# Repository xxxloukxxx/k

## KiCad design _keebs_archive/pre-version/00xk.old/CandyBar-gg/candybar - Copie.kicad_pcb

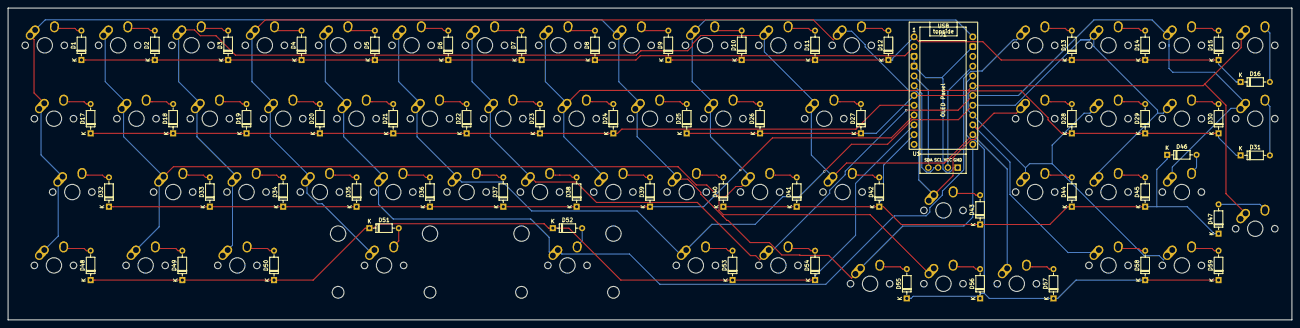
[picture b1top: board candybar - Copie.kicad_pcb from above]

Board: 2 copper layers, 333.4 x 81.0 mm, 120 parts (0 on the bottom side), 79 nets.

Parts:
D1, D2, D3, D4, D5, D6, D7, D8, D9, D10, D11, D12, D13, D14, D15, D16, D17, D18, D19, D20, D21, D22, D23, D24, D25, D26, D27, D28, D29, D30, D31, D32, D33, D34, D35, D36, D37, D38, D39, D40, D41, D42, D43, D44, D45, D46, D47, D48, D49, D50, D51, D52, D53, D54, D55, D56, D57, D58, D59: 1N4148; D_DO-35_SOD27_P7.62mm_Horizontal
J1: Conn_01x04_Socket; SSD1306-0.91-OLED-4pin-128x32
MX1, MX2, MX3, MX4, MX5, MX6, MX7, MX8, MX9, MX10, MX11, MX12, MX13, MX14, MX15, MX16, MX18, MX19, MX20, MX21, MX22, MX23, MX24, MX25, MX26, MX28, MX29, MX30, MX31, MX33, MX34, MX35, MX36, MX37, MX38, MX39, MX40, MX41, MX43, MX44, MX45, MX46, MX47, MX55, MX56, MX57, MX58, MX59: MX; MX-Alps-Hybrid-1U
MX17, MX42, MX48, MX49, MX50, MX53, MX54: MX; MX-Alps-Hybrid-1.25U
MX27, MX32: MX; MX-Alps-Hybrid-1.75U
MX51: MX; MX-Alps-Hybrid-2.75U-ReversedStabilizers
MX52: MX; MX-Alps-Hybrid-2.25U-ReversedStabilizers
U1: ProMicro; ProMicro_USBup

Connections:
COL1: MX1.1 (COL), MX9.1 (COL), MX17.1 (COL), MX25.1 (COL), MX32.1 (COL), MX40.1 (COL), MX48.1 (COL), MX55.1 (COL), U1.24 (B6)
COL2: MX2.1 (COL), MX10.1 (COL), MX18.1 (COL), MX26.1 (COL), MX33.1 (COL), MX41.1 (COL), MX49.1 (COL), MX56.1 (COL), U1.13 (B0)
COL3: MX3.1 (COL), MX11.1 (COL), MX19.1 (COL), MX27.1 (COL), MX34.1 (COL), MX42.1 (COL), MX50.1 (COL), MX57.1 (COL), U1.23 (B2)
COL4: MX4.1 (COL), MX12.1 (COL), MX20.1 (COL), MX28.1 (COL), MX35.1 (COL), MX43.1 (COL), MX51.1 (COL), MX58.1 (COL), U1.22 (B3)
COL5: MX5.1 (COL), MX13.1 (COL), MX21.1 (COL), MX29.1 (COL), MX36.1 (COL), MX44.1 (COL), MX52.1 (COL), MX59.1 (COL), U1.21 (B1)
COL6: MX6.1 (COL), MX14.1 (COL), MX22.1 (COL), MX30.1 (COL), MX37.1 (COL), MX45.1 (COL), MX53.1 (COL), U1.20 (F7)
COL7: MX7.1 (COL), MX15.1 (COL), MX23.1 (COL), MX31.1 (COL), MX38.1 (COL), MX46.1 (COL), MX54.1 (COL), U1.19 (F6)
COL8: MX8.1 (COL), MX16.1 (COL), MX24.1 (COL), MX39.1 (COL), MX47.1 (COL), U1.18 (F5)
GND: J1.1, U1.3 (GND), U1.4 (GND), U1.14 (GND)
unnamed: D1.2 (A), MX1.2 (ROW)
unnamed: D2.2 (A), MX2.2 (ROW)
unnamed: D3.2 (A), MX3.2 (ROW)
unnamed: D4.2 (A), MX4.2 (ROW)
unnamed: D5.2 (A), MX5.2 (ROW)
unnamed: D6.2 (A), MX6.2 (ROW)
unnamed: D7.2 (A), MX7.2 (ROW)
unnamed: D8.2 (A), MX8.2 (ROW)
unnamed: D9.2 (A), MX9.2 (ROW)
unnamed: D10.2 (A), MX10.2 (ROW)
unnamed: D11.2 (A), MX11.2 (ROW)
unnamed: D12.2 (A), MX12.2 (ROW)
unnamed: D13.2 (A), MX13.2 (ROW)
unnamed: D14.2 (A), MX14.2 (ROW)
unnamed: D15.2 (A), MX15.2 (ROW)
unnamed: D16.2 (A), MX16.2 (ROW)
unnamed: D17.2 (A), MX17.2 (ROW)
unnamed: D18.2 (A), MX18.2 (ROW)
unnamed: D19.2 (A), MX19.2 (ROW)
unnamed: D20.2 (A), MX20.2 (ROW)
unnamed: D21.2 (A), MX21.2 (ROW)
unnamed: D22.2 (A), MX22.2 (ROW)
unnamed: D23.2 (A), MX23.2 (ROW)
unnamed: D24.2 (A), MX24.2 (ROW)
unnamed: D25.2 (A), MX25.2 (ROW)
unnamed: D26.2 (A), MX26.2 (ROW)
unnamed: D27.2 (A), MX27.2 (ROW)
unnamed: D28.2 (A), MX28.2 (ROW)
unnamed: D29.2 (A), MX29.2 (ROW)
unnamed: D30.2 (A), MX30.2 (ROW)
unnamed: D31.2 (A), MX31.2 (ROW)
unnamed: D32.2 (A), MX32.2 (ROW)
unnamed: D33.2 (A), MX33.2 (ROW)
unnamed: D34.2 (A), MX34.2 (ROW)
unnamed: D35.2 (A), MX35.2 (ROW)
unnamed: D36.2 (A), MX36.2 (ROW)
unnamed: D37.2 (A), MX37.2 (ROW)
unnamed: D38.2 (A), MX38.2 (ROW)
unnamed: D39.2 (A), MX39.2 (ROW)
unnamed: D40.2 (A), MX40.2 (ROW)
unnamed: D41.2 (A), MX41.2 (ROW)
unnamed: D42.2 (A), MX42.2 (ROW)
unnamed: D43.2 (A), MX43.2 (ROW)
unnamed: D44.2 (A), MX44.2 (ROW)
unnamed: D45.2 (A), MX45.2 (ROW)
unnamed: D46.2 (A), MX46.2 (ROW)
unnamed: D47.2 (A), MX47.2 (ROW)
unnamed: D48.2 (A), MX48.2 (ROW)
unnamed: D49.2 (A), MX49.2 (ROW)
unnamed: D50.2 (A), MX50.2 (ROW)
unnamed: D51.2 (A), MX51.2 (ROW)
unnamed: D52.2 (A), MX52.2 (ROW)
unnamed: D53.2 (A), MX53.2 (ROW)
unnamed: D54.2 (A), MX54.2 (ROW)
unnamed: D55.2 (A), MX55.2 (ROW)
unnamed: D56.2 (A), MX56.2 (ROW)
unnamed: D57.2 (A), MX57.2 (ROW)
unnamed: D58.2 (A), MX58.2 (ROW)
unnamed: D59.2 (A), MX59.2 (ROW)
ROW1: D1.1 (K), D2.1 (K), D3.1 (K), D4.1 (K), D5.1 (K), D6.1 (K), D7.1 (K), D8.1 (K), U1.2 (D2-RX)
ROW2: D9.1 (K), D10.1 (K), D11.1 (K), D12.1 (K), D13.1 (K), D14.1 (K), D15.1 (K), D16.1 (K), U1.1 (D3-TX)
ROW3: D17.1 (K), D18.1 (K), D19.1 (K), D20.1 (K), D21.1 (K), D22.1 (K), D23.1 (K), D24.1 (K), U1.8 (C6)
ROW4: D25.1 (K), D26.1 (K), D27.1 (K), D28.1 (K), D29.1 (K), D30.1 (K), D31.1 (K), U1.7 (D4)
ROW5: D32.1 (K), D33.1 (K), D34.1 (K), D35.1 (K), D36.1 (K), D37.1 (K), D38.1 (K), D39.1 (K), U1.9 (D7)
ROW6: D40.1 (K), D41.1 (K), D42.1 (K), D43.1 (K), D44.1 (K), D45.1 (K), D46.1 (K), D47.1 (K), U1.11 (B4)
ROW7: D48.1 (K), D49.1 (K), D50.1 (K), D51.1 (K), D52.1 (K), D53.1 (K), D54.1 (K), U1.10 (E6)
ROW8: D55.1 (K), D56.1 (K), D57.1 (K), D58.1 (K), D59.1 (K), U1.17 (F4)
SCL: J1.3, U1.6 (D0)
SDA: J1.4, U1.5 (D1)
VCC: J1.2, U1.16 (VCC)

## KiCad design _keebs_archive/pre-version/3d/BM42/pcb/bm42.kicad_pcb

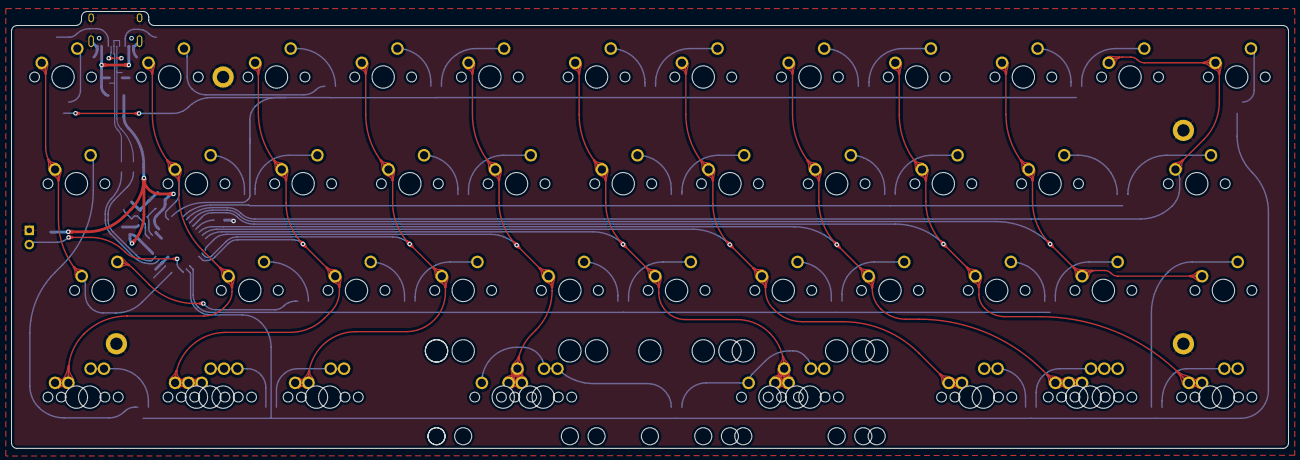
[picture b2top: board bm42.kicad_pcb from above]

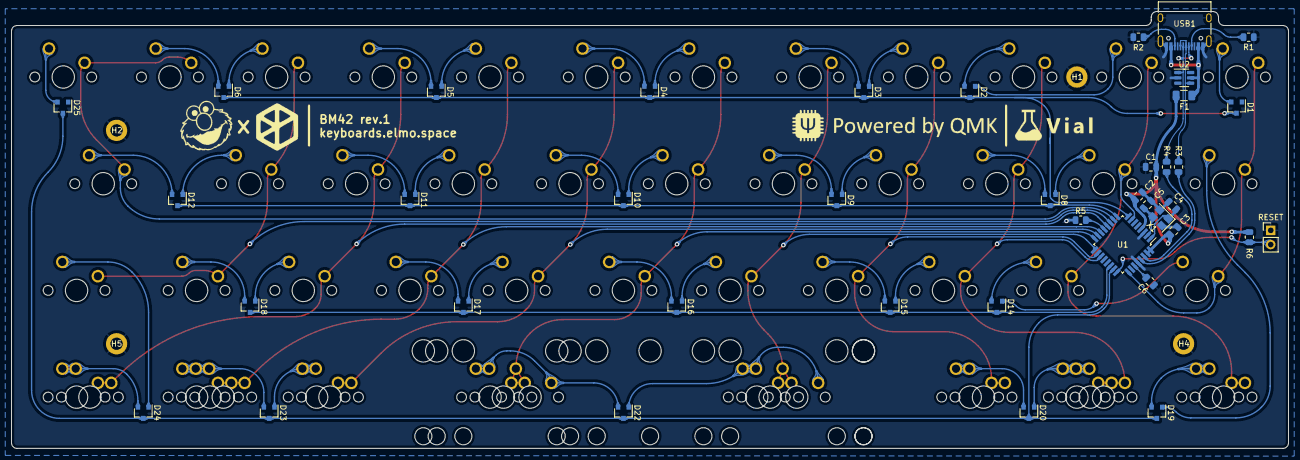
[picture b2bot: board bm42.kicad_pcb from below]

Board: 2 copper layers, 228.0 x 78.0 mm, 98 parts (44 on the bottom side), 71 nets.

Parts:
C1: 10uF; C_0805_2012Metric
C2, C3: 0.1uF; C_0805_2012Metric
C4, C5: 22pF; C_0805_2012Metric
C6: 1uF; C_0805_2012Metric
D1, D2, D3, D4, D5, D6, D8, D9, D10, D11, D12, D14, D15, D16, D17, D18, D19, D20, D22, D23, D24, D25: D_Small; D_SOT-23_ANK_norm
F1: Polyfuse_Small; Fuse_1206_3216Metric
H1, H2, H4, H5: MountingHole_Pad; MountingHole_2.2mm_M2_DIN965_Pad
MX1, MX2, MX3, MX4, MX5, MX6, MX7, MX8, MX9, MX10, MX11, MX13, MX14, MX15, MX16, MX17, MX18, MX19, MX20, MX21, MX24, MX25, MX26, MX27, MX28, MX29, MX30, MX31, MX32, MX35, MX41, MX43, MX50, MX51, MX52, MX54: MX-NoLED; MXOnly-1U-NoLED
MX12, MX33, MX34, MX36, MX40, MX42, MX49, MX53: MX-NoLED; MXOnly-1.25U-NoLED
MX22, MX23: MX-NoLED; MXOnly-1.75U-NoLED
MX37: MX-NoLED; MXOnly-3U-ReversedStabilizers-NoLED
MX39: MX-NoLED; MXOnly-2U-ReversedStabilizers-NoLED
MX44, MX47: MX-NoLED; MXOnly-2.75U-ReversedStabilizers-NoLED
MX45, MX46: MX-NoLED; MXOnly-2.25U-ReversedStabilizers-NoLED
MX48, MX55: MX-NoLED; MXOnly-1.5U-NoLED
R1, R2: 5.1k; R_0805_2012Metric
R3, R4: 22; R_0805_2012Metric
R5, R6: 10k; R_0805_2012Metric
RESET: RESET; PinHeader_1x02_P2.54mm_Vertical
U1: ATmega32U2-A; TQFP-32_7x7mm_P0.8mm
U2: SRV05-4; SOT-23-6
USB1: USB_C_Receptacle_USB2.0; USB_C_Receptacle_HRO_TYPE-C-31-M-12
X1: Crystal_GND24_Small; Crystal_SMD_3225-4Pin_3.2x2.5mm

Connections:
+5V: C1.1, C2.1, C3.1, F1.1, R6.2, U1.4 (VCC), U1.31 (UVCC), U1.32 (AVCC)
D+: R3.1, U2.4 (IO3), USB1.A6 (D+), USB1.B6 (D+)
D-: R4.1, U2.1 (IO1), USB1.A7 (D-), USB1.B7 (D-)
GND: C1.2, C2.2, C3.2, C4.2, C5.2, C6.2, H1.1, H2.1, H4.1, H5.1, R1.1, R2.1, R5.1, RESET.1, U1.3 (GND), U1.28 (UGND), U2.2 (VN), USB1.A1 (GND), USB1.A12 (GND), USB1.B1 (GND), USB1.B12 (GND), USB1.S1 (SHIELD), X1.2, X1.4
unnamed: C4.1, U1.1 (XTAL1), X1.1
unnamed: C5.1, U1.2 (PC0/XTAL2), X1.3
unnamed: C6.1, U1.27 (UCAP)
unnamed: D1.3 (A2), MX1.2 (ROW)
unnamed: D2.2 (A1), MX2.2 (ROW)
unnamed: D2.3 (A2), MX3.2 (ROW)
unnamed: D3.2 (A1), MX4.2 (ROW)
unnamed: D3.3 (A2), MX5.2 (ROW)
unnamed: D4.2 (A1), MX6.2 (ROW)
unnamed: D4.3 (A2), MX7.2 (ROW)
unnamed: D5.2 (A1), MX8.2 (ROW)
unnamed: D5.3 (A2), MX9.2 (ROW)
unnamed: D6.2 (A1), MX10.2 (ROW)
unnamed: D6.3 (A2), MX11.2 (ROW)
unnamed: D8.2 (A1), MX13.2 (ROW)
unnamed: D8.3 (A2), MX14.2 (ROW)
unnamed: D9.2 (A1), MX15.2 (ROW)
unnamed: D9.3 (A2), MX16.2 (ROW)
unnamed: D10.2 (A1), MX17.2 (ROW)
unnamed: D10.3 (A2), MX18.2 (ROW)
unnamed: D11.2 (A1), MX19.2 (ROW)
unnamed: D11.3 (A2), MX20.2 (ROW)
unnamed: D12.2 (A1), MX21.2 (ROW)
unnamed: D12.3 (A2), MX22.2 (ROW)
unnamed: D14.2 (A1), MX23.2 (ROW)
unnamed: D14.3 (A2), MX24.2 (ROW)
unnamed: D15.2 (A1), MX25.2 (ROW)
unnamed: D15.3 (A2), MX26.2 (ROW)
unnamed: D16.2 (A1), MX27.2 (ROW)
unnamed: D16.3 (A2), MX28.2 (ROW)
unnamed: D17.2 (A1), MX29.2 (ROW)
unnamed: D17.3 (A2), MX30.2 (ROW)
unnamed: D18.2 (A1), MX31.2 (ROW)
unnamed: D18.3 (A2), MX32.2 (ROW)
unnamed: D19.2 (A1), MX12.2 (ROW)
unnamed: D19.3 (A2), MX34.2 (ROW), MX48.2 (ROW)
unnamed: D20.2 (A1), MX35.2 (ROW), MX49.2 (ROW), MX50.2 (ROW)
unnamed: D20.3 (A2), MX36.2 (ROW), MX51.2 (ROW)
unnamed: D23.2 (A1), MX40.2 (ROW), MX52.2 (ROW)
unnamed: D23.3 (A2), MX41.2 (ROW), MX53.2 (ROW), MX54.2 (ROW)
unnamed: D24.2 (A1), MX33.2 (ROW)
unnamed: D24.3 (A2), MX42.2 (ROW), MX55.2 (ROW)
unnamed: D25.3 (A2), MX43.2 (ROW)
unnamed: R1.2, USB1.A5 (CC1)
unnamed: R2.2, USB1.B5 (CC2)
unnamed: R3.2, U1.29 (D+)
unnamed: R4.2, U1.30 (D-)
unnamed: R5.2, U1.13 (~HWB/PD7)
unnamed: R6.1, RESET.2, U1.24 (PC1/~RESET)
VCC: F1.2, U2.5 (VP), USB1.A4 (VBUS), USB1.A9 (VBUS), USB1.B4 (VBUS), USB1.B9 (VBUS)
col0: MX1.1 (COL), MX12.1 (COL), MX23.1 (COL), U1.25 (PC5)
col1: MX2.1 (COL), MX13.1 (COL), MX24.1 (COL), MX34.1 (COL), MX48.1 (COL), U1.7 (PD1)
col2: MX3.1 (COL), MX14.1 (COL), MX25.1 (COL), MX35.1 (COL), MX49.1 (COL), MX50.1 (COL), U1.19 (PB5)
col3: MX4.1 (COL), MX15.1 (COL), MX26.1 (COL), MX36.1 (COL), MX51.1 (COL), U1.18 (PB4)
col4: MX5.1 (COL), MX16.1 (COL), MX27.1 (COL), MX37.1 (COL), MX44.1 (COL), MX46.2 (ROW), U1.17 (PB3)
col5: MX6.1 (COL), MX17.1 (COL), MX28.1 (COL), MX39.1 (COL), MX45.1 (COL), MX47.2 (ROW), U1.16 (PB2)
col6: MX7.1 (COL), MX18.1 (COL), MX29.1 (COL), MX40.1 (COL), MX52.1 (COL), U1.15 (PB1)
col7: MX8.1 (COL), MX19.1 (COL), MX30.1 (COL), MX41.1 (COL), MX53.1 (COL), MX54.1 (COL), U1.14 (PB0)
col8: MX9.1 (COL), MX20.1 (COL), MX31.1 (COL), MX42.1 (COL), MX55.1 (COL), U1.12 (PD6)
col9: MX10.1 (COL), MX21.1 (COL), MX32.1 (COL), MX33.1 (COL), U1.11 (PD5)
col10: MX11.1 (COL), MX22.1 (COL), MX43.1 (COL), U1.10 (PD4)
row0: D1.1 (K), D2.1 (K), D3.1 (K), D4.1 (K), D5.1 (K), D6.1 (K), U1.8 (PD2)
row1: D8.1 (K), D9.1 (K), D10.1 (K), D11.1 (K), D12.1 (K), U1.9 (PD3)
row2: D14.1 (K), D15.1 (K), D16.1 (K), D17.1 (K), D18.1 (K), U1.22 (PC7)
row3: D19.1 (K), D20.1 (K), D22.1 (K), D23.1 (K), D24.1 (K), D25.1 (K), U1.23 (PC6)
spc1: D22.2 (A1), MX37.2 (ROW), MX44.2 (ROW), MX46.1 (COL)
spc2: D22.3 (A2), MX39.2 (ROW), MX45.2 (ROW), MX47.1 (COL)

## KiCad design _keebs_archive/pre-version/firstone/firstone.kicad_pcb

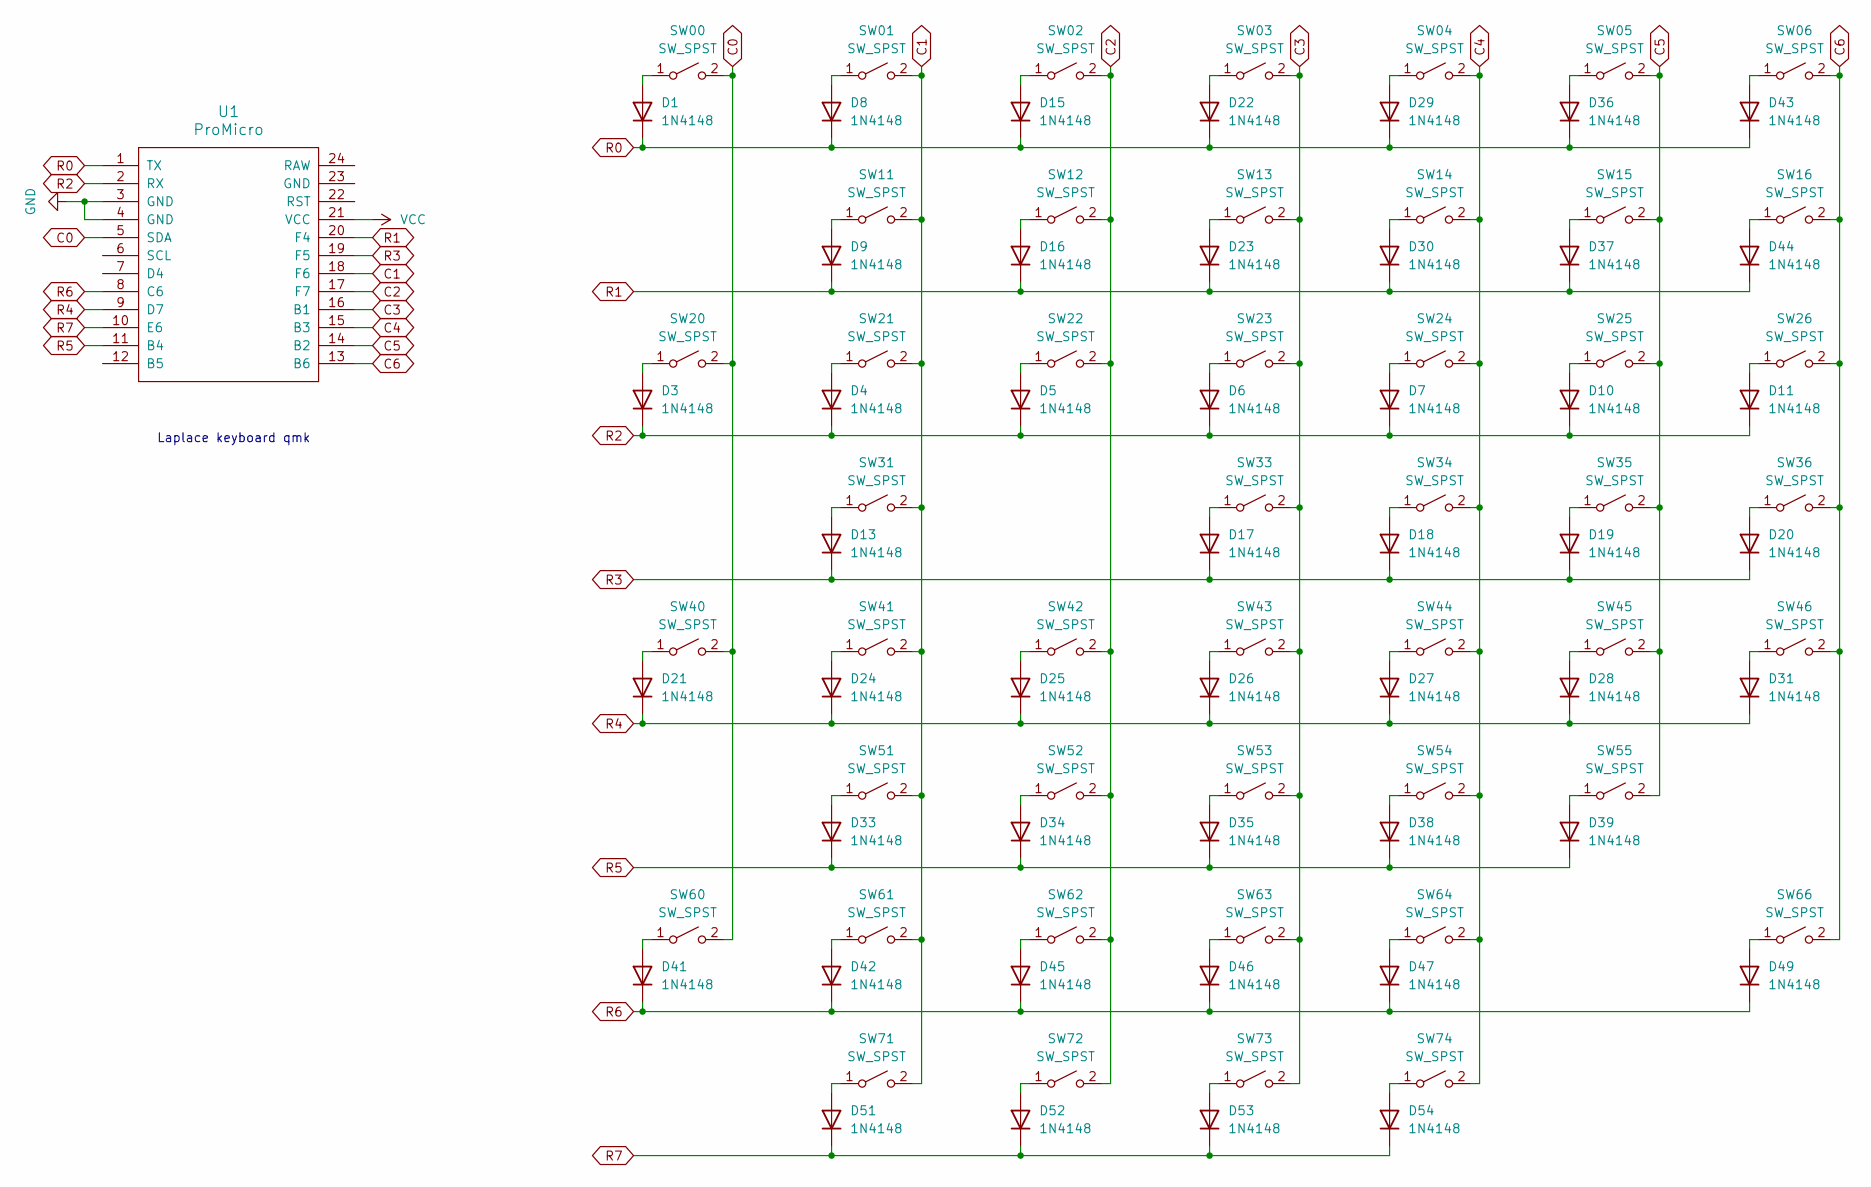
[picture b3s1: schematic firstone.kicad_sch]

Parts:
D1, D3, D4, D5, D6, D7, D8, D9, D10, D11, D13, D15, D16, D17, D18, D19, D20, D21, D22, D23, D24, D25, D26, D27, D28, D29, D30, D31, D33, D34, D35, D36, D37, D38, D39, D41, D42, D43, D44, D45, D46, D47, D49, D51, D52, D53, D54: 1N4148; D_DO-35_SOD27_P7.62mm_Horizontal
SW00, SW01, SW02, SW03, SW04, SW05, SW06, SW11, SW12, SW13, SW14, SW15, SW16, SW20, SW21, SW22, SW23, SW24, SW25, SW26, SW31, SW33, SW34, SW35, SW36, SW40, SW41, SW42, SW43, SW44, SW45, SW46, SW51, SW52, SW53, SW54, SW55, SW60, SW61, SW62, SW63, SW64, SW66, SW71, SW72, SW73, SW74: SW_SPST; SW_Cherry_MX_PCB
U1: ProMicro

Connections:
C0: SW00.2 (B), SW20.2 (B), SW40.2 (B), SW60.2 (B), U1.5 (SDA)
C1: SW01.2 (B), SW11.2 (B), SW21.2 (B), SW31.2 (B), SW41.2 (B), SW51.2 (B), SW61.2 (B), SW71.2 (B), U1.18 (F6)
C2: SW02.2 (B), SW12.2 (B), SW22.2 (B), SW42.2 (B), SW52.2 (B), SW62.2 (B), SW72.2 (B), U1.17 (F7)
C3: SW03.2 (B), SW13.2 (B), SW23.2 (B), SW33.2 (B), SW43.2 (B), SW53.2 (B), SW63.2 (B), SW73.2 (B), U1.16 (B1)
C4: SW04.2 (B), SW14.2 (B), SW24.2 (B), SW34.2 (B), SW44.2 (B), SW54.2 (B), SW64.2 (B), SW74.2 (B), U1.15 (B3)
C5: SW05.2 (B), SW15.2 (B), SW25.2 (B), SW35.2 (B), SW45.2 (B), SW55.2 (B), U1.14 (B2)
C6: SW06.2 (B), SW16.2 (B), SW26.2 (B), SW36.2 (B), SW46.2 (B), SW66.2 (B), U1.13 (B6)
GND: U1.3 (GND), U1.4 (GND)
unnamed: D1.2 (A), SW00.1 (A)
unnamed: D3.2 (A), SW20.1 (A)
unnamed: D4.2 (A), SW21.1 (A)
unnamed: D5.2 (A), SW22.1 (A)
unnamed: D6.2 (A), SW23.1 (A)
unnamed: D7.2 (A), SW24.1 (A)
unnamed: D8.2 (A), SW01.1 (A)
unnamed: D9.2 (A), SW11.1 (A)
unnamed: D10.2 (A), SW25.1 (A)
unnamed: D11.2 (A), SW26.1 (A)
unnamed: D13.2 (A), SW31.1 (A)
unnamed: D15.2 (A), SW02.1 (A)
unnamed: D16.2 (A), SW12.1 (A)
unnamed: D17.2 (A), SW33.1 (A)
unnamed: D18.2 (A), SW34.1 (A)
unnamed: D19.2 (A), SW35.1 (A)
unnamed: D20.2 (A), SW36.1 (A)
unnamed: D21.2 (A), SW40.1 (A)
unnamed: D22.2 (A), SW03.1 (A)
unnamed: D23.2 (A), SW13.1 (A)
unnamed: D24.2 (A), SW41.1 (A)
unnamed: D25.2 (A), SW42.1 (A)
unnamed: D26.2 (A), SW43.1 (A)
unnamed: D27.2 (A), SW44.1 (A)
unnamed: D28.2 (A), SW45.1 (A)
unnamed: D29.2 (A), SW04.1 (A)
unnamed: D30.2 (A), SW14.1 (A)
unnamed: D31.2 (A), SW46.1 (A)
unnamed: D33.2 (A), SW51.1 (A)
unnamed: D34.2 (A), SW52.1 (A)
unnamed: D35.2 (A), SW53.1 (A)
unnamed: D36.2 (A), SW05.1 (A)
unnamed: D37.2 (A), SW15.1 (A)
unnamed: D38.2 (A), SW54.1 (A)
unnamed: D39.2 (A), SW55.1 (A)
unnamed: D41.2 (A), SW60.1 (A)
unnamed: D42.2 (A), SW61.1 (A)
unnamed: D43.2 (A), SW06.1 (A)
unnamed: D44.2 (A), SW16.1 (A)
unnamed: D45.2 (A), SW62.1 (A)
unnamed: D46.2 (A), SW63.1 (A)
unnamed: D47.2 (A), SW64.1 (A)
unnamed: D49.2 (A), SW66.1 (A)
unnamed: D51.2 (A), SW71.1 (A)
unnamed: D52.2 (A), SW72.1 (A)
unnamed: D53.2 (A), SW73.1 (A)
unnamed: D54.2 (A), SW74.1 (A)
R0: D1.1 (K), D8.1 (K), D15.1 (K), D22.1 (K), D29.1 (K), D36.1 (K), D43.1 (K), U1.1 (TX)
R1: D9.1 (K), D16.1 (K), D23.1 (K), D30.1 (K), D37.1 (K), D44.1 (K), U1.20 (F4)
R2: D3.1 (K), D4.1 (K), D5.1 (K), D6.1 (K), D7.1 (K), D10.1 (K), D11.1 (K), U1.2 (RX)
R3: D13.1 (K), D17.1 (K), D18.1 (K), D19.1 (K), D20.1 (K), U1.19 (F5)
R4: D21.1 (K), D24.1 (K), D25.1 (K), D26.1 (K), D27.1 (K), D28.1 (K), D31.1 (K), U1.9 (D7)
R5: D33.1 (K), D34.1 (K), D35.1 (K), D38.1 (K), D39.1 (K), U1.11 (B4)
R6: D41.1 (K), D42.1 (K), D45.1 (K), D46.1 (K), D47.1 (K), D49.1 (K), U1.8 (C6)
R7: D51.1 (K), D52.1 (K), D53.1 (K), D54.1 (K), U1.10 (E6)
VCC: U1.21 (VCC)

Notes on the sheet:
Laplace keyboard qmk

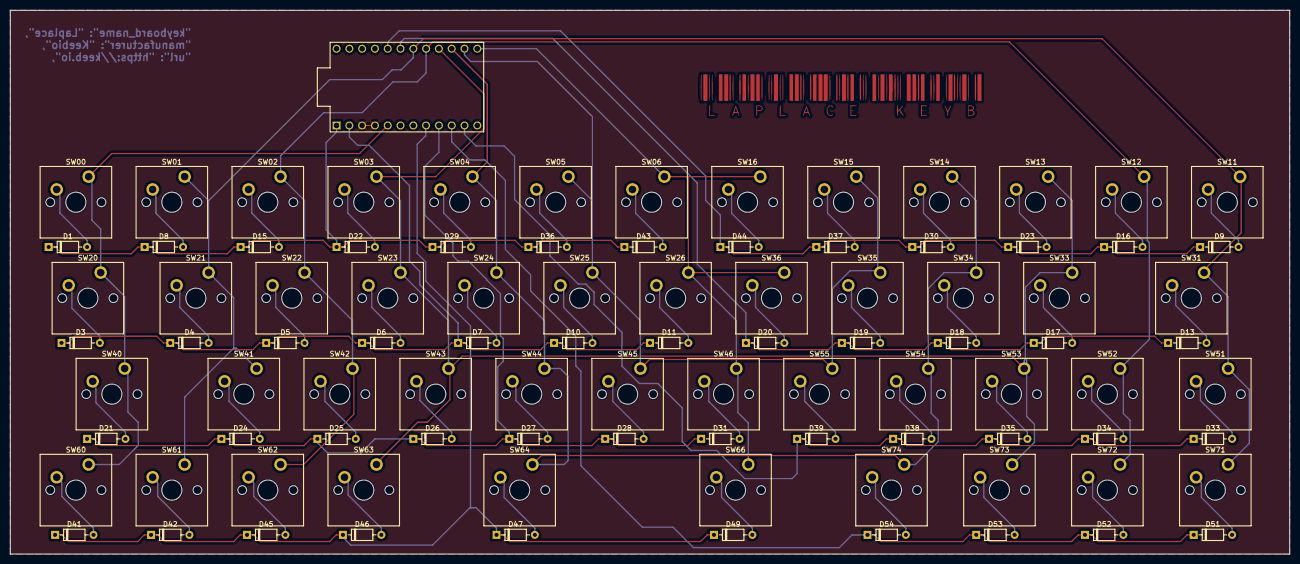
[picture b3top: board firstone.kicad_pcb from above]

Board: 2 copper layers, 254.0 x 108.0 mm, 95 parts (0 on the bottom side), 63 nets.

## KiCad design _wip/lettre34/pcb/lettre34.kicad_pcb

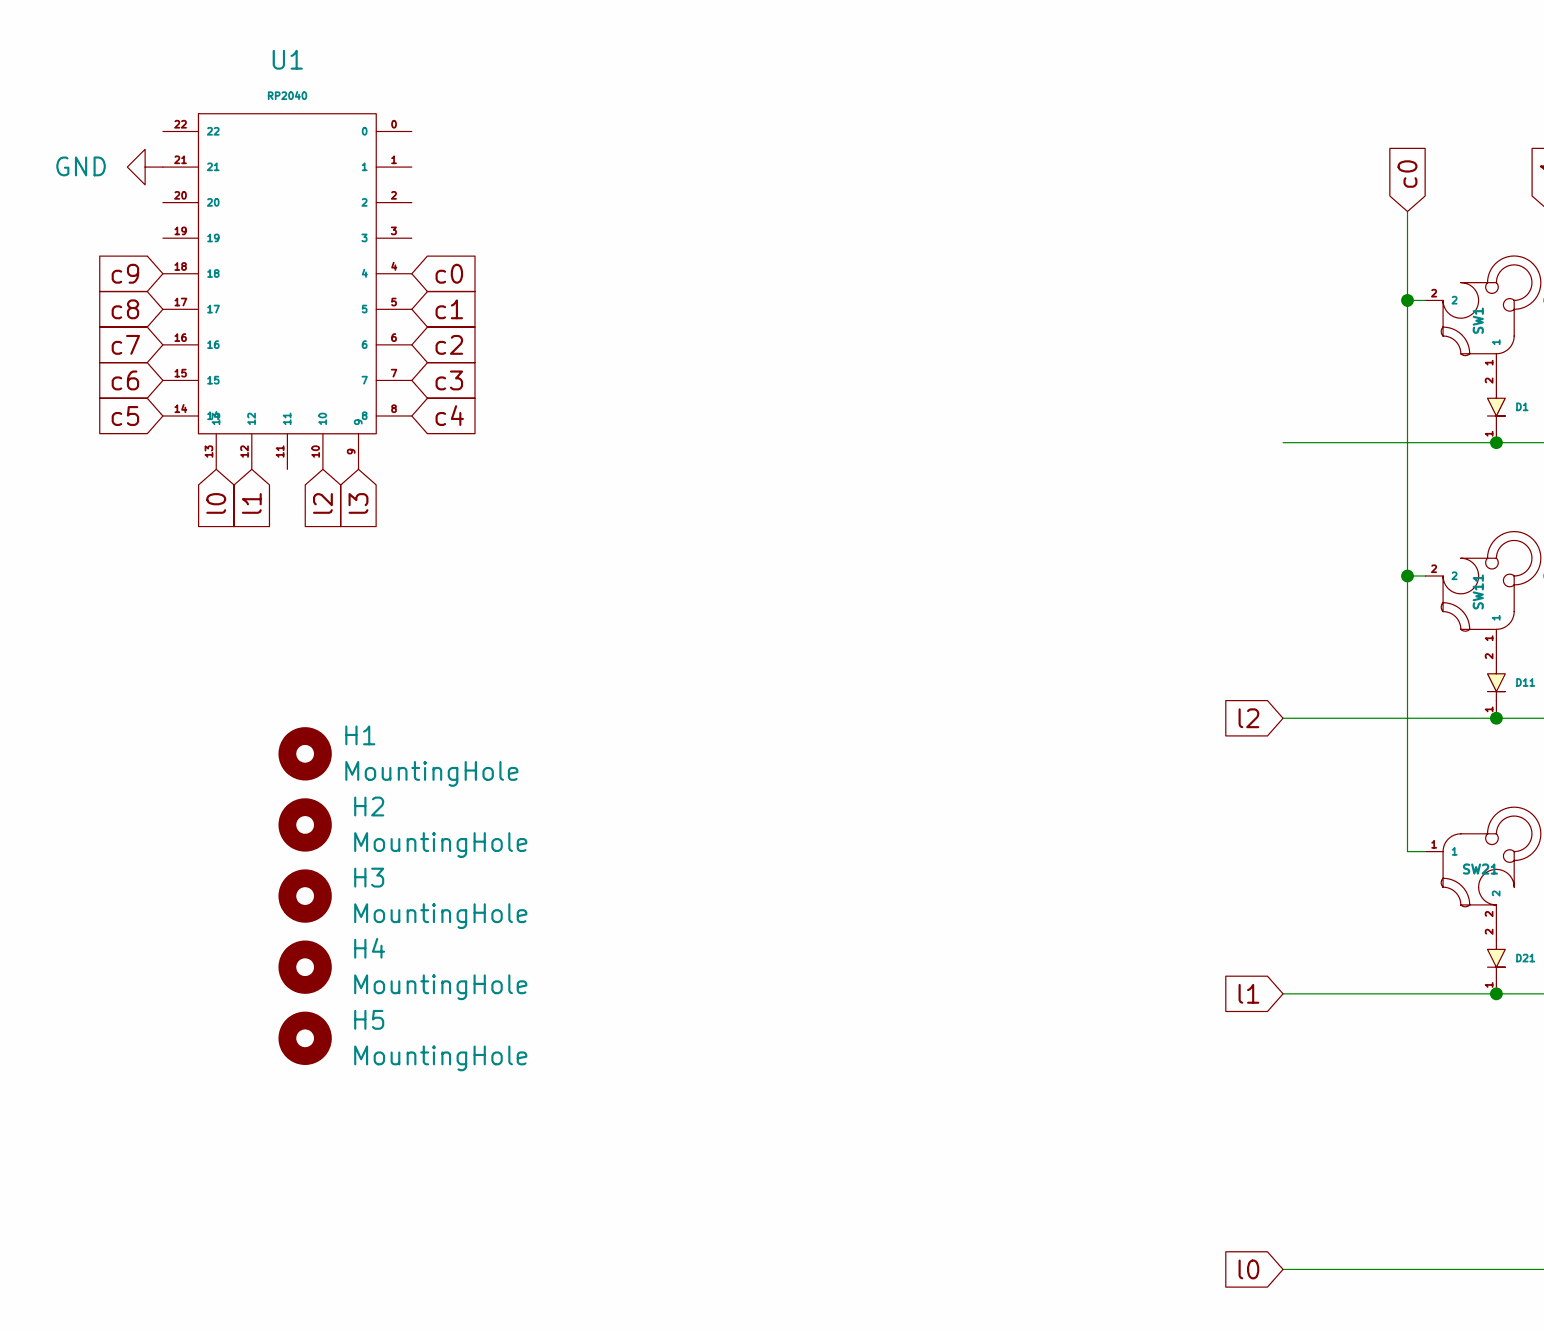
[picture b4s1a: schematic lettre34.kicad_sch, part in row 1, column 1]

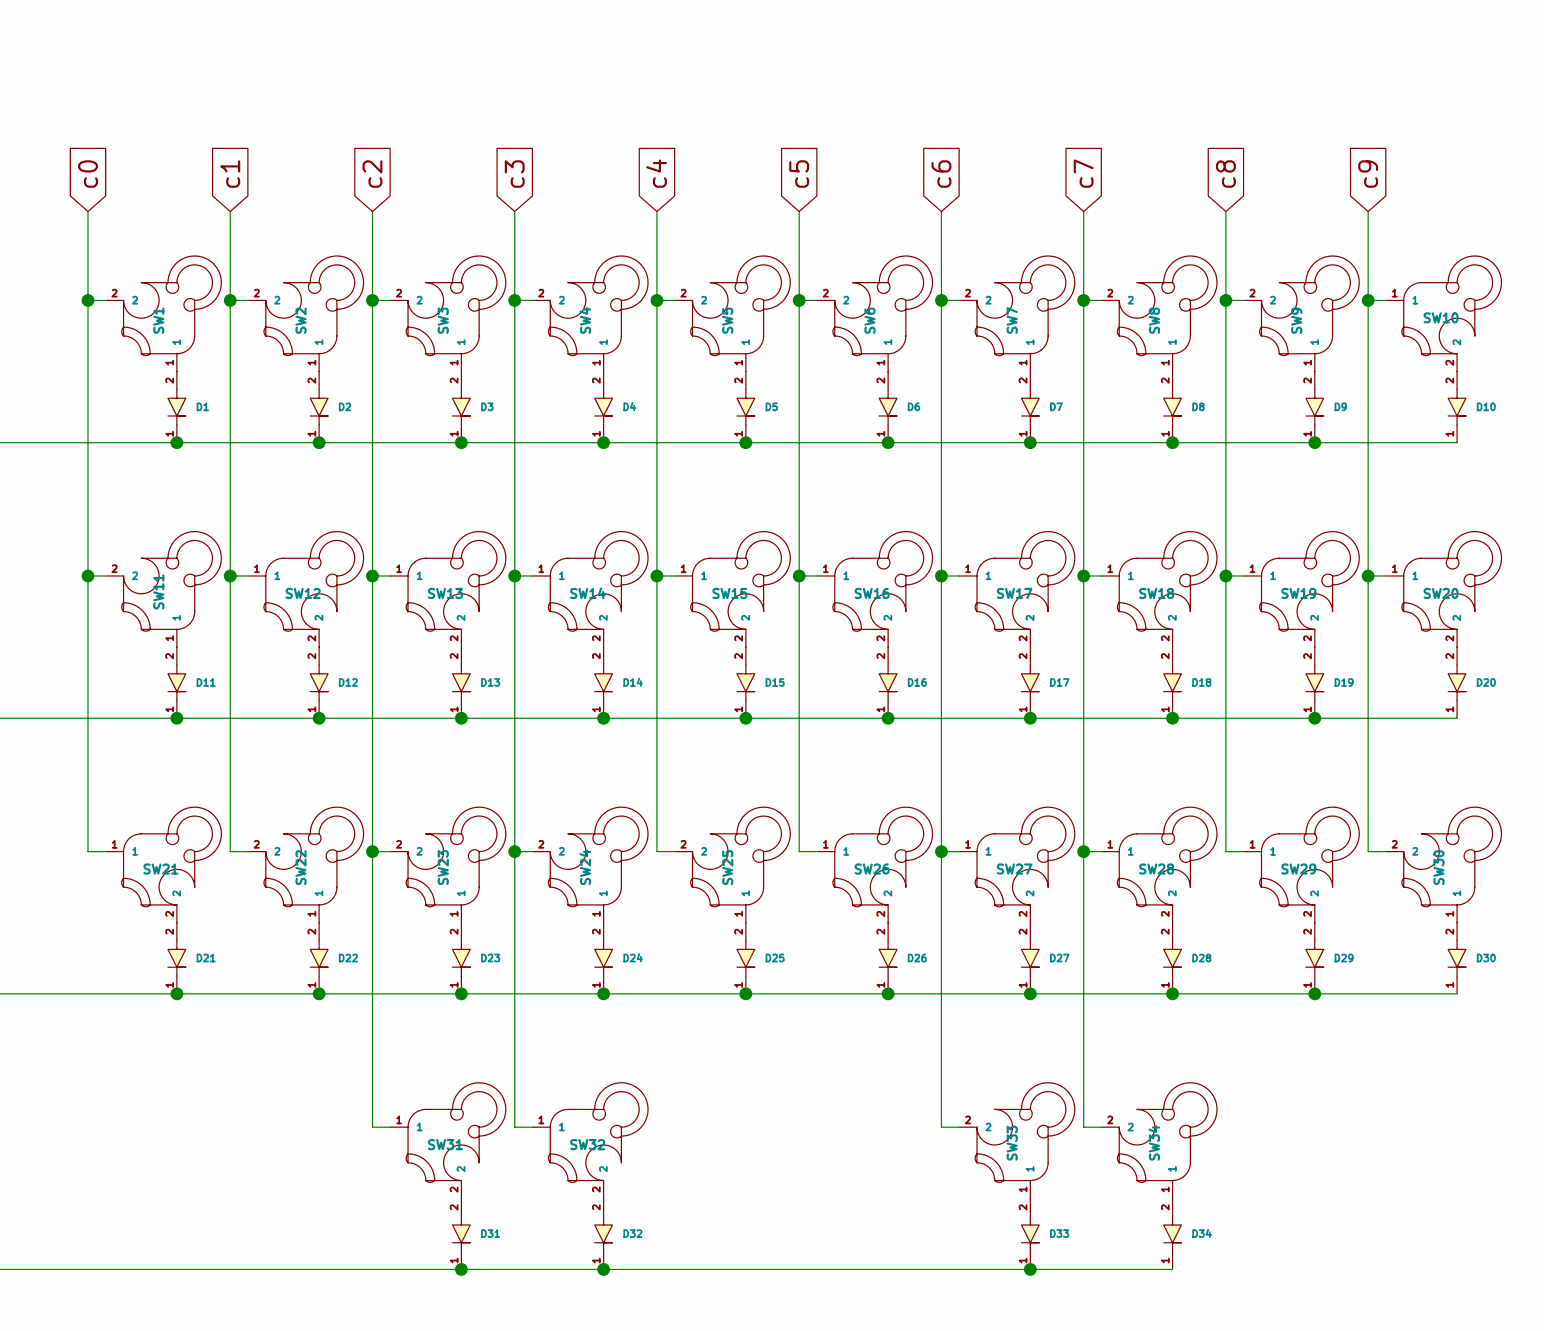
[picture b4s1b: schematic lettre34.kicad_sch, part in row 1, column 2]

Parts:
D1, D2, D3, D4, D5, D6, D7, D8, D9, D10, D11, D12, D13, D14, D15, D16, D17, D18, D19, D20, D21, D22, D23, D24, D25, D26, D27, D28, D29, D30, D31, D32, D33, D34: Diode
H1, H2, H3, H4, H5: MountingHole; MountingHole_2.2mm_M2
SW1, SW2, SW3, SW4, SW5, SW6, SW7, SW8, SW9, SW10, SW11, SW12, SW13, SW14, SW15, SW16, SW17, SW18, SW19, SW20, SW21, SW22, SW23, SW24, SW25, SW26, SW27, SW28, SW29, SW30, SW31, SW34: key; MX-5pin
SW32, SW33: key; MX-5pin_stab
U1: RP2040

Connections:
GND: U1.21
unnamed: D1.1, D2.1, D3.1, D4.1, D5.1, D6.1, D7.1, D8.1, D9.1, D10.1
unnamed: D5.2, SW5.1
unnamed: D6.2, SW6.1
unnamed: D7.2, SW7.1
unnamed: D8.2, SW8.1
unnamed: D9.2, SW9.1
unnamed: D10.2, SW10.2
unnamed: D12.2, SW12.2
unnamed: D13.2, SW13.2
unnamed: D14.2, SW14.2
unnamed: D15.2, SW15.2
unnamed: D16.2, SW16.2
unnamed: D18.2, SW18.2
unnamed: D19.2, SW19.2
unnamed: D20.2, SW20.2
unnamed: D21.2, SW21.2
unnamed: D22.2, SW22.1
unnamed: D23.2, SW23.1
unnamed: D24.2, SW24.1
unnamed: D25.2, SW25.1
unnamed: D26.2, SW26.2
unnamed: D27.2, SW27.2
unnamed: D28.2, SW28.2
unnamed: D30.2, SW30.1
unnamed: D31.2, SW31.2
unnamed: D32.2, SW32.2
unnamed: D33.2, SW33.1
unnamed: D34.2, SW34.1
unnamed: D1.2, SW1.1
unnamed: D2.2, SW2.1
unnamed: D3.2, SW3.1
unnamed: D4.2, SW4.1
unnamed: D11.2, SW11.1
unnamed: D17.2, SW17.2
unnamed: D29.2, SW29.2
c0: SW1.2, SW11.2, SW21.1, U1.4
c1: SW2.2, SW12.1, SW22.2, U1.5
c2: SW3.2, SW13.1, SW23.2, SW31.1, U1.6
c3: SW4.2, SW14.1, SW24.2, SW32.1, U1.7
c4: SW5.2, SW15.1, SW25.2, U1.8
c5: SW6.2, SW16.1, SW26.1, U1.14
c6: SW7.2, SW17.1, SW27.1, SW33.2, U1.15
c7: SW8.2, SW18.1, SW28.1, SW34.2, U1.16
c8: SW9.2, SW19.1, SW29.1, U1.17
c9: SW10.1, SW20.1, SW30.2, U1.18
l0: D31.1, D32.1, D33.1, D34.1, U1.13
l1: D21.1, D22.1, D23.1, D24.1, D25.1, D26.1, D27.1, D28.1, D29.1, D30.1, U1.12
l2: D11.1, D12.1, D13.1, D14.1, D15.1, D16.1, D17.1, D18.1, D19.1, D20.1, U1.10
l3: U1.9

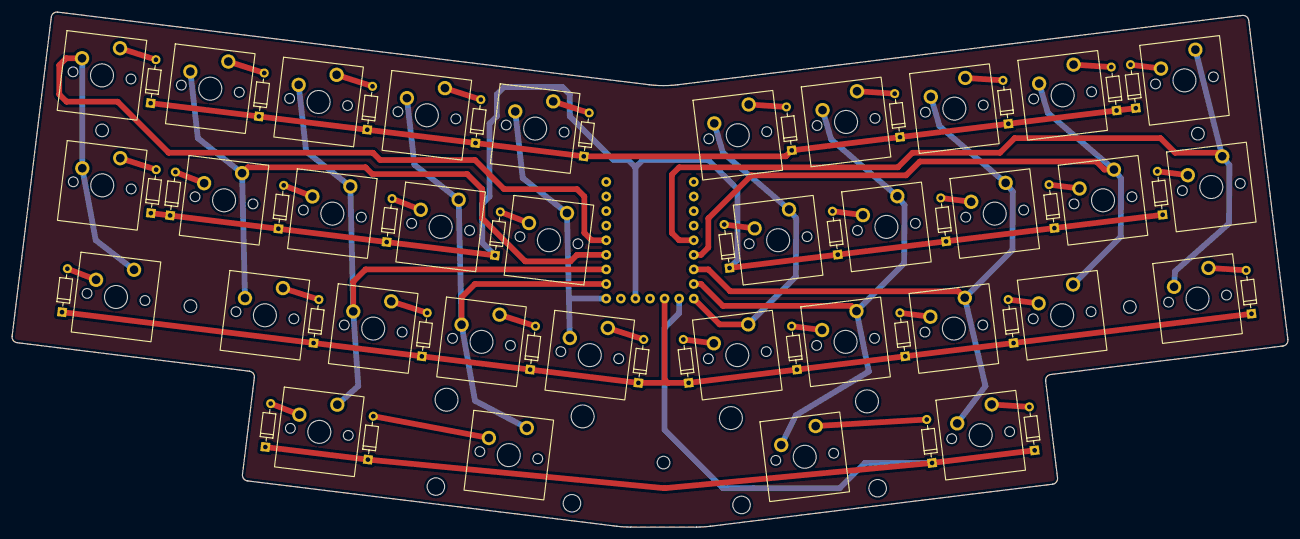
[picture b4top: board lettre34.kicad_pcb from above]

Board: 2 copper layers, 222.2 x 89.7 mm, 74 parts (1 on the bottom side), 48 nets.

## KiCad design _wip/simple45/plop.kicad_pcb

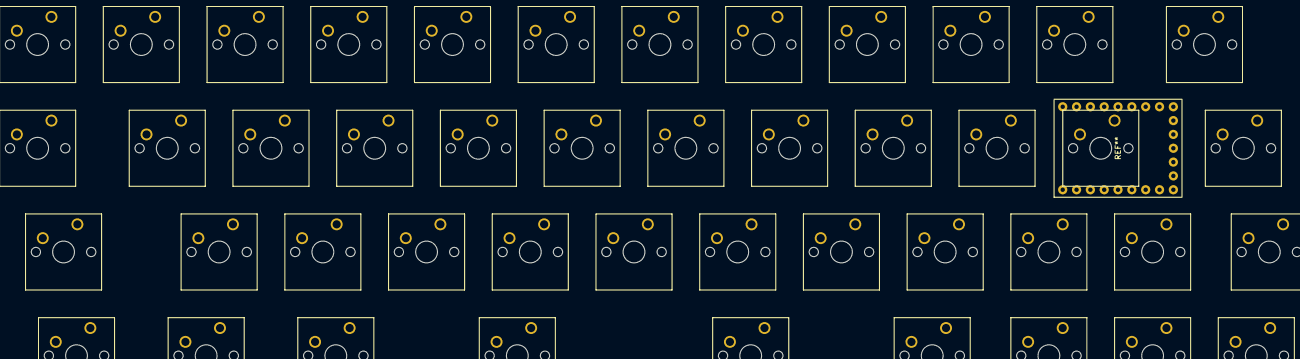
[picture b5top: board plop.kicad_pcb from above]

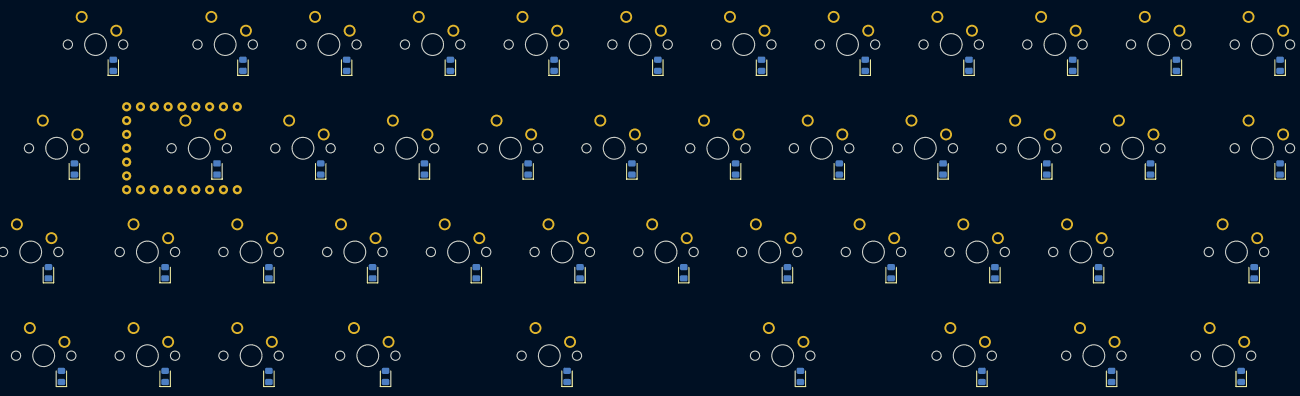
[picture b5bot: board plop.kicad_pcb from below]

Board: 2 copper layers, 90 parts (45 on the bottom side), 61 nets, no tracks yet.

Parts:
D0, D1, D2, D3, D4, D5, D6, D7, D8, D9, D10, D11, D12, D13, D14, D15, D16, D17, D18, D19, D20, D21, D22, D23, D24, D25, D26, D27, D28, D29, D30, D31, D32, D33, D34, D35, D36, D37, D38, D39, D40, D41, D42, D43, D44: D; D_0805_2012Metric_Pad1.15x1.40mm_HandSolder
K0: ~,`; SW_Cherry_MX_1.00u_PCB
K1: Q; SW_Cherry_MX_1.00u_PCB
K2: W; SW_Cherry_MX_1.00u_PCB
K3: E; SW_Cherry_MX_1.00u_PCB
K4: R; SW_Cherry_MX_1.00u_PCB
K5: T; SW_Cherry_MX_1.00u_PCB
K6: Y; SW_Cherry_MX_1.00u_PCB
K7: U; SW_Cherry_MX_1.00u_PCB
K8: I; SW_Cherry_MX_1.00u_PCB
K9: O; SW_Cherry_MX_1.00u_PCB
K10: P; SW_Cherry_MX_1.00u_PCB
K11: |,\; SW_Cherry_MX_1.50u_PCB
K12: Tab; SW_Cherry_MX_1.50u_PCB
K13: A; SW_Cherry_MX_1.00u_PCB
K14: S; SW_Cherry_MX_1.00u_PCB
K15: D; SW_Cherry_MX_1.00u_PCB
K16: F; SW_Cherry_MX_1.00u_PCB
K17: G; SW_Cherry_MX_1.00u_PCB
K18: H; SW_Cherry_MX_1.00u_PCB
K19: J; SW_Cherry_MX_1.00u_PCB
K20: K; SW_Cherry_MX_1.00u_PCB
K21: L; SW_Cherry_MX_1.00u_PCB
K22: ",'; SW_Cherry_MX_1.00u_PCB
K23: Caps Lock; SW_Cherry_MX_1.75u_PCB
K24: Backspace; SW_Cherry_MX_2.00u_PCB
K25: Z; SW_Cherry_MX_1.00u_PCB
K26: X; SW_Cherry_MX_1.00u_PCB
K27: C; SW_Cherry_MX_1.00u_PCB
K28: V; SW_Cherry_MX_1.00u_PCB
K29: B; SW_Cherry_MX_1.00u_PCB
K30: N; SW_Cherry_MX_1.00u_PCB
K31: M; SW_Cherry_MX_1.00u_PCB
K32: <,,; SW_Cherry_MX_1.00u_PCB
K33: >,.; SW_Cherry_MX_1.00u_PCB
K34: <i class='kb kb-Arrows-Up'></i>; SW_Cherry_MX_1.00u_PCB
K35: Blank; SW_Cherry_MX_1.25u_PCB
K36: Ctrl; SW_Cherry_MX_1.25u_PCB
K37: Win; SW_Cherry_MX_1.25u_PCB
K38, K41: Alt; SW_Cherry_MX_1.25u_PCB
K39: Blank; SW_Cherry_MX_2.25u_PCB
K40: Enter; SW_Cherry_MX_2.25u_PCB
K42: <i class='kb kb-Arrows-Left'></i>; SW_Cherry_MX_1.00u_PCB
K43: <i class='kb kb-Arrows-Down'></i>; SW_Cherry_MX_1.00u_PCB
K44: <i class='kb kb-Arrows-Right'></i>; SW_Cherry_MX_1.00u_PCB

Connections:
/Col_0: K0.1, K12.1, K24.1, K36.1
/Col_1: K1.1, K13.1, K25.1, K37.1
/Col_2: K2.1, K14.1, K26.1, K38.1
/Col_3: K3.1, K15.1, K27.1, K39.1
/Col_4: K4.1, K16.1, K28.1, K40.1
/Col_5: K5.1, K17.1, K29.1, K41.1
/Col_6: K6.1, K18.1, K30.1, K42.1
/Col_7: K7.1, K19.1, K31.1, K43.1
/Col_8: K8.1, K20.1, K32.1, K44.1
/Col_9: K9.1, K21.1, K33.1
/Col_10: K10.1, K22.1, K34.1
/Col_11: K11.1, K23.1, K35.1
/Row_0: D0.1, D1.1, D2.1, D3.1, D4.1, D5.1, D6.1, D7.1, D8.1, D9.1, D10.1, D11.1
/Row_1: D12.1, D13.1, D14.1, D15.1, D16.1, D17.1, D18.1, D19.1, D20.1, D21.1, D22.1, D23.1
/Row_2: D24.1, D25.1, D26.1, D27.1, D28.1, D29.1, D30.1, D31.1, D32.1, D33.1, D34.1, D35.1
/Row_3: D36.1, D37.1, D38.1, D39.1, D40.1, D41.1, D42.1, D43.1, D44.1
unnamed: D0.2, K0.2
unnamed: D1.2, K1.2
unnamed: D2.2, K2.2
unnamed: D3.2, K3.2
unnamed: D4.2, K4.2
unnamed: D5.2, K5.2
unnamed: D6.2, K6.2
unnamed: D7.2, K7.2
unnamed: D8.2, K8.2
unnamed: D9.2, K9.2
unnamed: D10.2, K10.2
unnamed: D11.2, K11.2
unnamed: D12.2, K12.2
unnamed: D13.2, K13.2
unnamed: D14.2, K14.2
unnamed: D15.2, K15.2
unnamed: D16.2, K16.2
unnamed: D17.2, K17.2
unnamed: D18.2, K18.2
unnamed: D19.2, K19.2
unnamed: D20.2, K20.2
unnamed: D21.2, K21.2
unnamed: D22.2, K22.2
unnamed: D23.2, K23.2
unnamed: D24.2, K24.2
unnamed: D25.2, K25.2
unnamed: D26.2, K26.2
unnamed: D27.2, K27.2
unnamed: D28.2, K28.2
unnamed: D29.2, K29.2
unnamed: D30.2, K30.2
unnamed: D31.2, K31.2
unnamed: D32.2, K32.2
unnamed: D33.2, K33.2
unnamed: D34.2, K34.2
unnamed: D35.2, K35.2
unnamed: D36.2, K36.2
unnamed: D37.2, K37.2
unnamed: D38.2, K38.2
unnamed: D39.2, K39.2
unnamed: D40.2, K40.2
unnamed: D41.2, K41.2
unnamed: D42.2, K42.2
unnamed: D43.2, K43.2
unnamed: D44.2, K44.2
